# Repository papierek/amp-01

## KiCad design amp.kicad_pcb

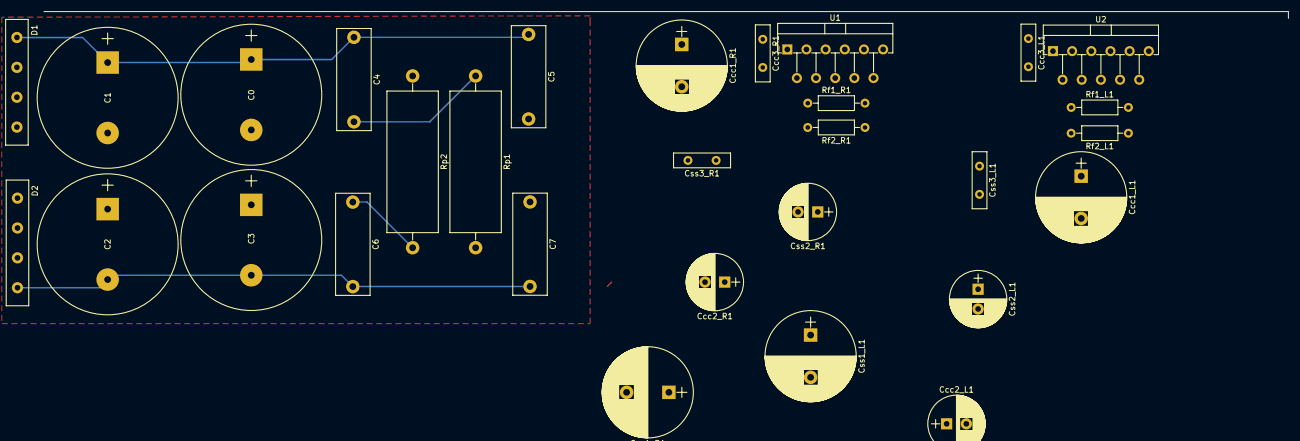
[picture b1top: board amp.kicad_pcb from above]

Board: 2 copper layers, 30 parts (0 on the bottom side), 10 nets.

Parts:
C0, C1, C2, C3: 10m; CP_Radial_D25.0mm_P12.50mm_SnapIn
C4, C5, C6, C7: 0.1u; C_Rect_L18.0mm_W6.0mm_P15.00mm_FKS3_FKP3
Ccc1_L1, Ccc1_R1: 1000u; CP_Radial_D16.0mm_P7.50mm
Ccc2_L1, Ccc2_R1: 22u; CP_Radial_D10.0mm_P3.50mm
Ccc3_L1, Ccc3_R1: 2.2u; C_Disc_D10.0mm_W2.5mm_P5.00mm
Css1_L1, Css1_R1: 1000u; CP_Radial_D16.0mm_P7.50mm
Css2_L1, Css2_R1: 22u; CP_Radial_D10.0mm_P3.50mm
Css3_L1, Css3_R1: 2.2u; C_Disc_D10.0mm_W2.5mm_P5.00mm
D1, D2: 400V/25A; rect_bridge_4x24
Rf1_L1, Rf1_R1: 20k; R_Axial_DIN0207_L6.3mm_D2.5mm_P10.16mm_Horizontal
Rf2_L1, Rf2_R1: 1k; R_Axial_DIN0207_L6.3mm_D2.5mm_P10.16mm_Horizontal
Rp1, Rp2: 1; R_Axial_Power_L25.0mm_W9.0mm_P30.48mm
U1, U2: LM3886T; Multiwatt-11_Vertical_StaggeredType2

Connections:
unnamed: Rf1_L1.1, U2.3
unnamed: Rf1_R1.1, U1.3
unnamed: C4.2, Rp1.1
unnamed: C6.1, Rp2.2
unnamed: Rf1_R1.2, Rf2_R1.1, U1.9
unnamed: Rf1_L1.2, Rf2_L1.1, U2.9
PWR_GND: Ccc1_L1.2, Ccc1_R1.2, Ccc2_L1.2, Ccc2_R1.2, Ccc3_L1.2, Ccc3_R1.2, Css1_L1.1, Css1_R1.1, Css2_L1.1, Css2_R1.1, Css3_L1.2, Css3_R1.1, U1.7, U2.7
VCC: C0.1, C1.1, C4.1, C5.1, Ccc1_L1.1, Ccc1_R1.1, Ccc2_L1.1, Ccc2_R1.1, Ccc3_L1.1, Ccc3_R1.1, D1.1, U1.1, U1.5, U2.1, U2.5
VSS: C2.2, C3.2, C6.2, C7.2, Css1_L1.2, Css1_R1.2, Css2_L1.2, Css2_R1.2, Css3_L1.1, Css3_R1.2, D2.2, U1.4, U2.4
common_gnd: C0.2, C1.2, C2.1, C3.1, C5.2, C7.1, D1.2, D2.1, Rp1.2, Rp2.1

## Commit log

2017-06-15 initial-commit
2017-06-15 move
